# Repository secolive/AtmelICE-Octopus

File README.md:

"Octopus" adapter for Atmel-ICE
===============================

Introduction
------------

this project provides KiCad files for the implementation of an adapter board for use with the Atmel-ICE JTAG debugger.
It provides the following features:

- 0.1" headers with standard pinouts
- Specific VCCIO connector for using a probe
- Jumpers to select VCCIO from the appropriate connectors depending on the use case
- VCCIO comparator and limiter for current nominal voltages: 1.8V, 2.5V, 3.0V, 3.3V, 3.7V, 5.0V
- Voltage boosting to power the LEDs when VCCIO voltages below 3.3V are used

### Motivation

The Atmel-ICE provides two 0.05" headers, for which it's unfortunately difficult to get the appropriate cables. Some
versions of the Atmel-ICE come with a "squid" adapter, but are significantly more expensive.

Boards
------

This project contains two different boards that will assemble and work together as a single "product":

- ATMEL-ICE-Octopus: this is the main adapter board, including all circuits implementing VCCIO selection and limiting

- JTAG-MINI_ADAPTER: 0.1" to 0.05" adapter for standard 10-pin JTAG connectors

Connectors
----------

The following connectors are provided by the Octopus:
- J11: 20-pin 0.1" Multi-ICE JTAG header
- J12: 10-pin 0.1" JTAG connector for ARM
- J13: 10-pin 0.1" JTAG connector for Atmel AVR
- J14: 6-pin 0.1" connector for misc AVR protocols: SPI, debugWire, aWire, PDI, UPDI, TPI
- J15: 4-pin 0.1" header matching Arduino's SWD port
- J16: 1-pin 0.1" header to use as VCCIO probe, typically in conjunction with J15 which does not provide any VCCIO;
  note that J15&J16 together work as a 6-pin 0.1" header combining SWD with VCCIO probe
- J17: 2-pin 0.1" socket to be used for adhoc connections
- J18: 6-pin 0.1" socket to be used for adhoc connections
- J6: 1-pin 0.1" socket to be used as a test point for the VTG provided to Atmel-ICE

VCCIO
-----

The Atmel-ICE needs to be fed with the VCCIO corresponding to the board under test, so that it will work at the same
logic level as the CPU being inspected.

To avoid damage to your CPU, it is important that the VCCIO that the Atmel-ICE uses does not exceed the level actually
used by the board. The octopus helps providing safety as follows:

- The reference VCCIO voltage can come from one of three sources, depending on your use case; these sources are: the
  JTAG connectors, the AVR misc connector, and the VCCIO probe. Use the appropriate source depending in your use case
  to ensure that you're using the VCCIO that matches the component you're connecting to.

- Select the appropriate source using the corresponding jumper; common use cases are:
    * when using a JTAG cable: put the jumper in the JTAG position;
    * when using the AVR misc cable, and your board runs on 5.0V: put the jumper in the SPI position;
    * when using the AVR misc cable, and your board runs on something else than 5.0V: put the jumper in the PROBE
      position, and use the PROBE connector in addition to the SPI cable;
    * when using the SWD cable: put the jumper in the PROBE position, and use the PROBE connector in addition to the SPI
      cable.

- You need to further configure the nominal voltage you're expecting to use with your device, using the appropriate
  jumper. The on-board detection logic will use this configuration to decide whether it is safe to propagate the VCCIO
  voltage to the Atmel-ICE VTG input, as follows:
    * if the input VCCIO matches the nominal voltage range, it is send to the Atmel-ICE, and the green "OK" LED will
      be lit;
    * if the input VCCIO is below the nominal voltage range, it is send to the Atmel-ICE nevertheless, but the amber
      "Below" LED will be lit;
    * otherwise, i.e. if the input VCCIO is above the nominal voltage range, no voltage is sent to the Atmel-ICE, because
      it is considered as a fault which could result in using a voltage higher than the expected VCCIO of the target
      device. In this case, the red "Above" LED will be lit.

Simplified Variants
-------------------

Depending on your use cases, you might not need all the features of the board; for example, perhaps you  need only the
various 0.1" connectors, but don't care about the voltage limiting. Reducing the feature set enables you to skip some
components and hence reduce the cost. Three features are optional:

- VCCIO monitoring and limiting; this main feature can by bypassed altogether, and the selected VCCIO can be sent
  directly as VTG to the Atmel-ICE. You will then have to ensure that you select the proper VCCIO signal, and that it
  does not exceed the target device voltage.

- Status output of the VCCIO monitoring and limiting; obviously, if you don't perform any monitoring and limiting, you
  won't need any status LEDs. Note that it's technically possible to have some voltage monitoring, without limiting,
  meaning VCCIO will always be sent as VTG to the Atmel-ICE, but the Above/OK/Below LEDs will still indicate whether the
  voltage is in the intended range.

- Voltage boosting to power LEDs when input voltage is below 3.3V. Obviously, if you don't want any status LEDs, you
  don't need any voltage boosting.

Altogether, this means the following variants are possible:

- Variant 1a: VCCIO limiting, monitoring with LEDS, voltage boosting
- Variant 1b: VCCIO limiting, monitoring with LEDS, no voltage boosting
- Variant 2a: VCCIO monitoring with LEDs, no limiting, voltage boosting
- Variant 2b: VCCIO monitoring with LEDs, no limiting, no voltage boosting
- Variant 3: VCCIO limiting, no monitoring, no LEDs
- Variant 4: no VCCIO limiting, no monitoring, no LEDs

The following table describes, for which variant, which components can be skipped, and how to position the solder
jumpers JP1 and JP2.

| Variant | *10-*39       | *40-*49            | *50-*59 | *60-*79 | *80-*89 | JP1 2-3 | JP2 2-3 |
|---------|---------------|--------------------|---------|---------|---------|---------|---------|
| 1a      |               |                    |         |         |         |         |         |
| 1b      |               |                    |         |  skip   |         |         |    X    |
| 2a      | skip Q12, C12 |                    |  skip   |         |         |    X    |         |
| 2b      | skip Q12, C12 |                    |  skip   |  skip   |         |    X    |    X    |
| 3       |               | skip Q41, R41, *42 |         |  skip   |  skip   |         |         |
| 4       | skip          | skip               |  skip   |  skip   |  skip   |    X    |         |

Note that wildcards are used to designate any component with the given number, and when ranges are provided, any
component of any type within the given number range should be skipped. The JP columns indicate when the corresponding
jumper needs to have its pads 2 and 3 bridged.

Regarding JP1 and JP2, note that by default they are always bridged in the 1-2 position. It is not necessary to cut this
traced bridging, as long as the corresponding components are skipped according to the table above.

!! Do not forget to verify the proper jumper settings when adding new components to the board, e.g. in a later stage !!

Assembling
----------

The main board is composed of two different parts; when looking at the front:
- the right-hand side contains the black plate, which is meant to be connected to the Atmel-ICE
- the main part is the squid adapter itself

The back plate can be separated from the main part by breaking off the two break tabs. Connect the back plate to the 
main plate using angled 2mm-pitch headers. 

The assembled octopus adapter can then be plugged atop the Atmel-ICE; both products can be assembled using 8mm-long
spacers using M2.5 threads and screws (plastic recommended), as follows:

On the target device, use the adapter when using a standard Atmel 0.05" header; the adapter is designed to fit an
Arduino Due board and not collide with a shield, as follows:

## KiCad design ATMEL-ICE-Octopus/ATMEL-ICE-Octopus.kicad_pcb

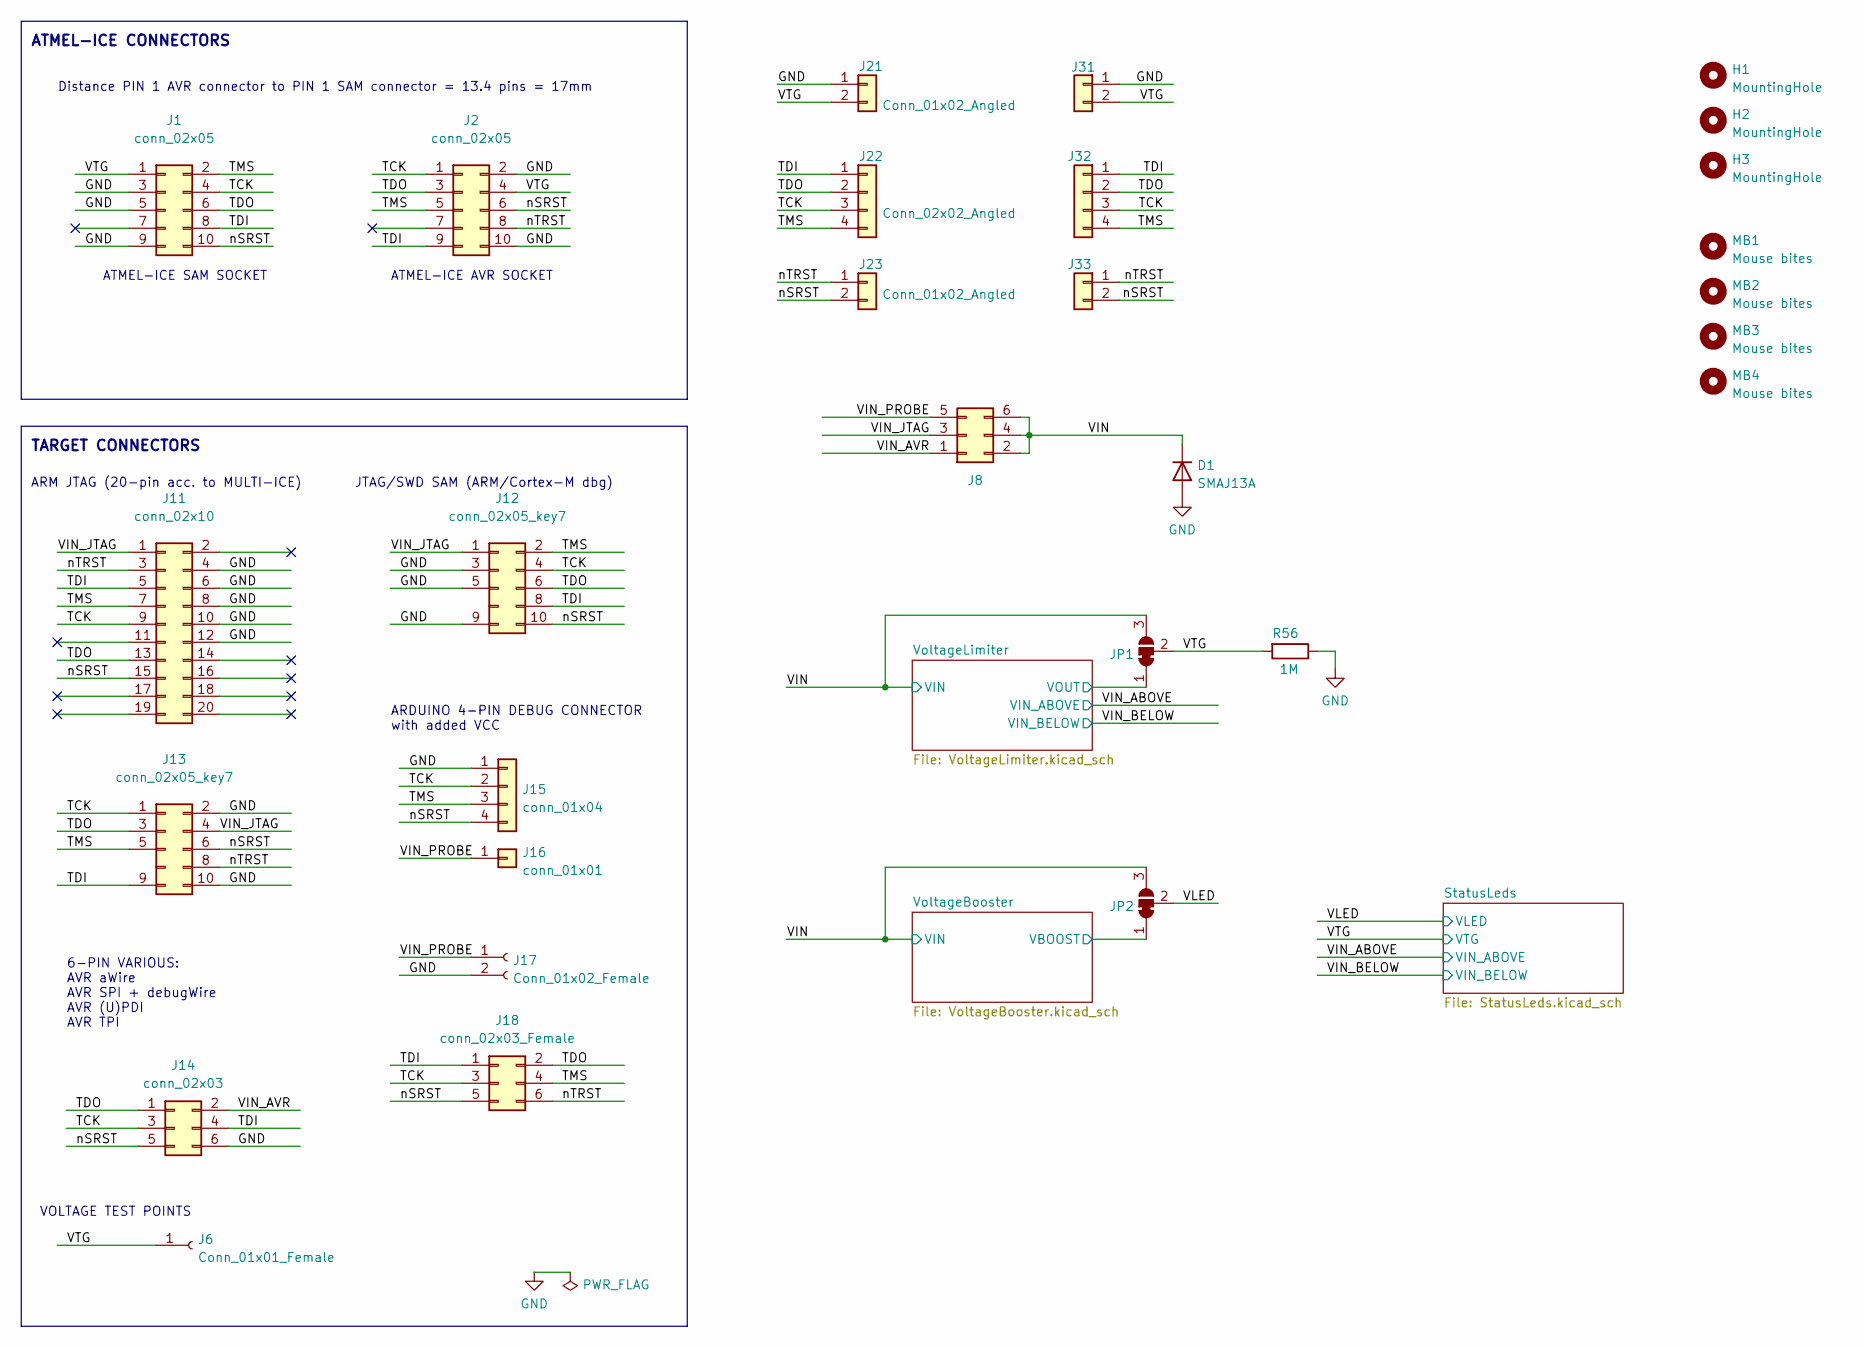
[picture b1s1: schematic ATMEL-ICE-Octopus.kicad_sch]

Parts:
D1: SMAJ13A; D_SMA+SMP_Handsoldering
H1, H2, H3: MountingHole; MountingHole_2.5mm
J1, J2: conn_02x05; PinSocket_2x05_P1.27mm_Vertical_AtmelICE_WithTab
J6: Conn_01x01_Female; PinSocket_1x01_P2.54mm_Vertical
J8: PinHeader_2x03_P2.54mm_Horizontal_Jumper
J11: conn_02x10; IDC-Header_2x10_P2.54mm_Vertical
J12, J13: conn_02x05_key7; IDC-Header_2x05_P2.54mm_Vertical_Key7
J14: conn_02x03; IDC-Header_2x03_P2.54mm_Vertical
J15: conn_01x04; PinHeader_1x04_P2.54mm_Vertical
J16: conn_01x01; PinHeader_1x01_P2.54mm_Vertical
J17: Conn_01x02_Female; PinSocket_1x02_P2.54mm_Vertical
J18: conn_02x03_Female; PinSocket_2x03_P2.54mm_Vertical
J21, J23: Conn_01x02_Angled; PinHeader_1x02_P2.00mm_Horizontal
J22: Conn_02x02_Angled; PinHeader_2x02_P2.00mm_Horizontal
J31, J33: Conn_01x02_Angled; PinHeader_1x02_P2.00mm_Angled
J32: Conn_02x02_Angled; PinHeader_2x02_P2.00mm_Angled
JP1, JP2: SolderJumper_3_Bridged12; SolderJumper-3_P1.3mm_Bridged2Bar12_RoundedPad1.0x1.5mm_Num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
MB1, MB2, MB3, MB4: Mouse bites; mouse-bite-3x4mm-slot
R56: 1M; R_0805_2012Metric_Pad1.20x1.40mm_HandSolder

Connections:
/TCK: J1.4, J2.1, J11.9, J12.4, J13.1, J14.3, J15.2, J18.3, J22.3, J32.3
/TDI: J1.8, J2.9, J11.5, J12.8, J13.9, J14.4, J18.1, J22.1, J32.1
/TDO: J1.6, J2.3, J11.13, J12.6, J13.3, J14.1, J18.2, J22.2, J32.2
/TMS: J1.2, J2.5, J11.7, J12.2, J13.5, J15.3, J18.4, J22.4, J32.4
/VIN: D1.1 (K), J8.2, J8.4, J8.6, JP1.3 (B), JP2.3 (B); also elsewhere on the board
/VIN_AVR: J8.1, J14.2
/VIN_JTAG: J8.3, J11.1, J12.1, J13.4
/VIN_PROBE: J8.5, J16.1, J17.1
/VLED: JP2.2 (C); also elsewhere on the board
/VTG: J1.1, J2.4, J6.1, J21.2, J31.2, JP1.2 (C), R56.2; also elsewhere on the board
/VoltageBooster/VBOOST: JP2.1 (A); also elsewhere on the board
/VoltageLimiter/VOUT: JP1.1 (A); also elsewhere on the board
/nSRST: J1.10, J2.6, J11.15, J12.10, J13.6, J14.5, J15.4, J18.5, J23.2, J33.2
/nTRST: J2.8, J11.3, J13.8, J18.6, J23.1, J33.1
GND: D1.2 (A), J1.3, J1.5, J1.9, J2.2, J2.10, J11.4, J11.6, J11.8, J11.10, J11.12, J12.3, J12.5, J12.9, J13.2, J13.10, J14.6, J15.1, J17.2, J21.1, J31.1, R56.1; also elsewhere on the board

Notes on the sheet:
ARDUINO 4-PIN DEBUG CONNECTOR with added VCC
Distance PIN 1 AVR connector to PIN 1 SAM connector = 13.4 pins = 17mm
6-PIN VARIOUS: AVR aWire AVR SPI + debugWire AVR (U)PDI AVR TPI
ARM JTAG (20-pin acc. to MULTI-ICE)
ATMEL-ICE CONNECTORS
ATMEL-ICE AVR SOCKET
VOLTAGE TEST POINTS
TARGET CONNECTORS
ATMEL-ICE SAM SOCKET
JTAG/SWD SAM (ARM/Cortex-M dbg)

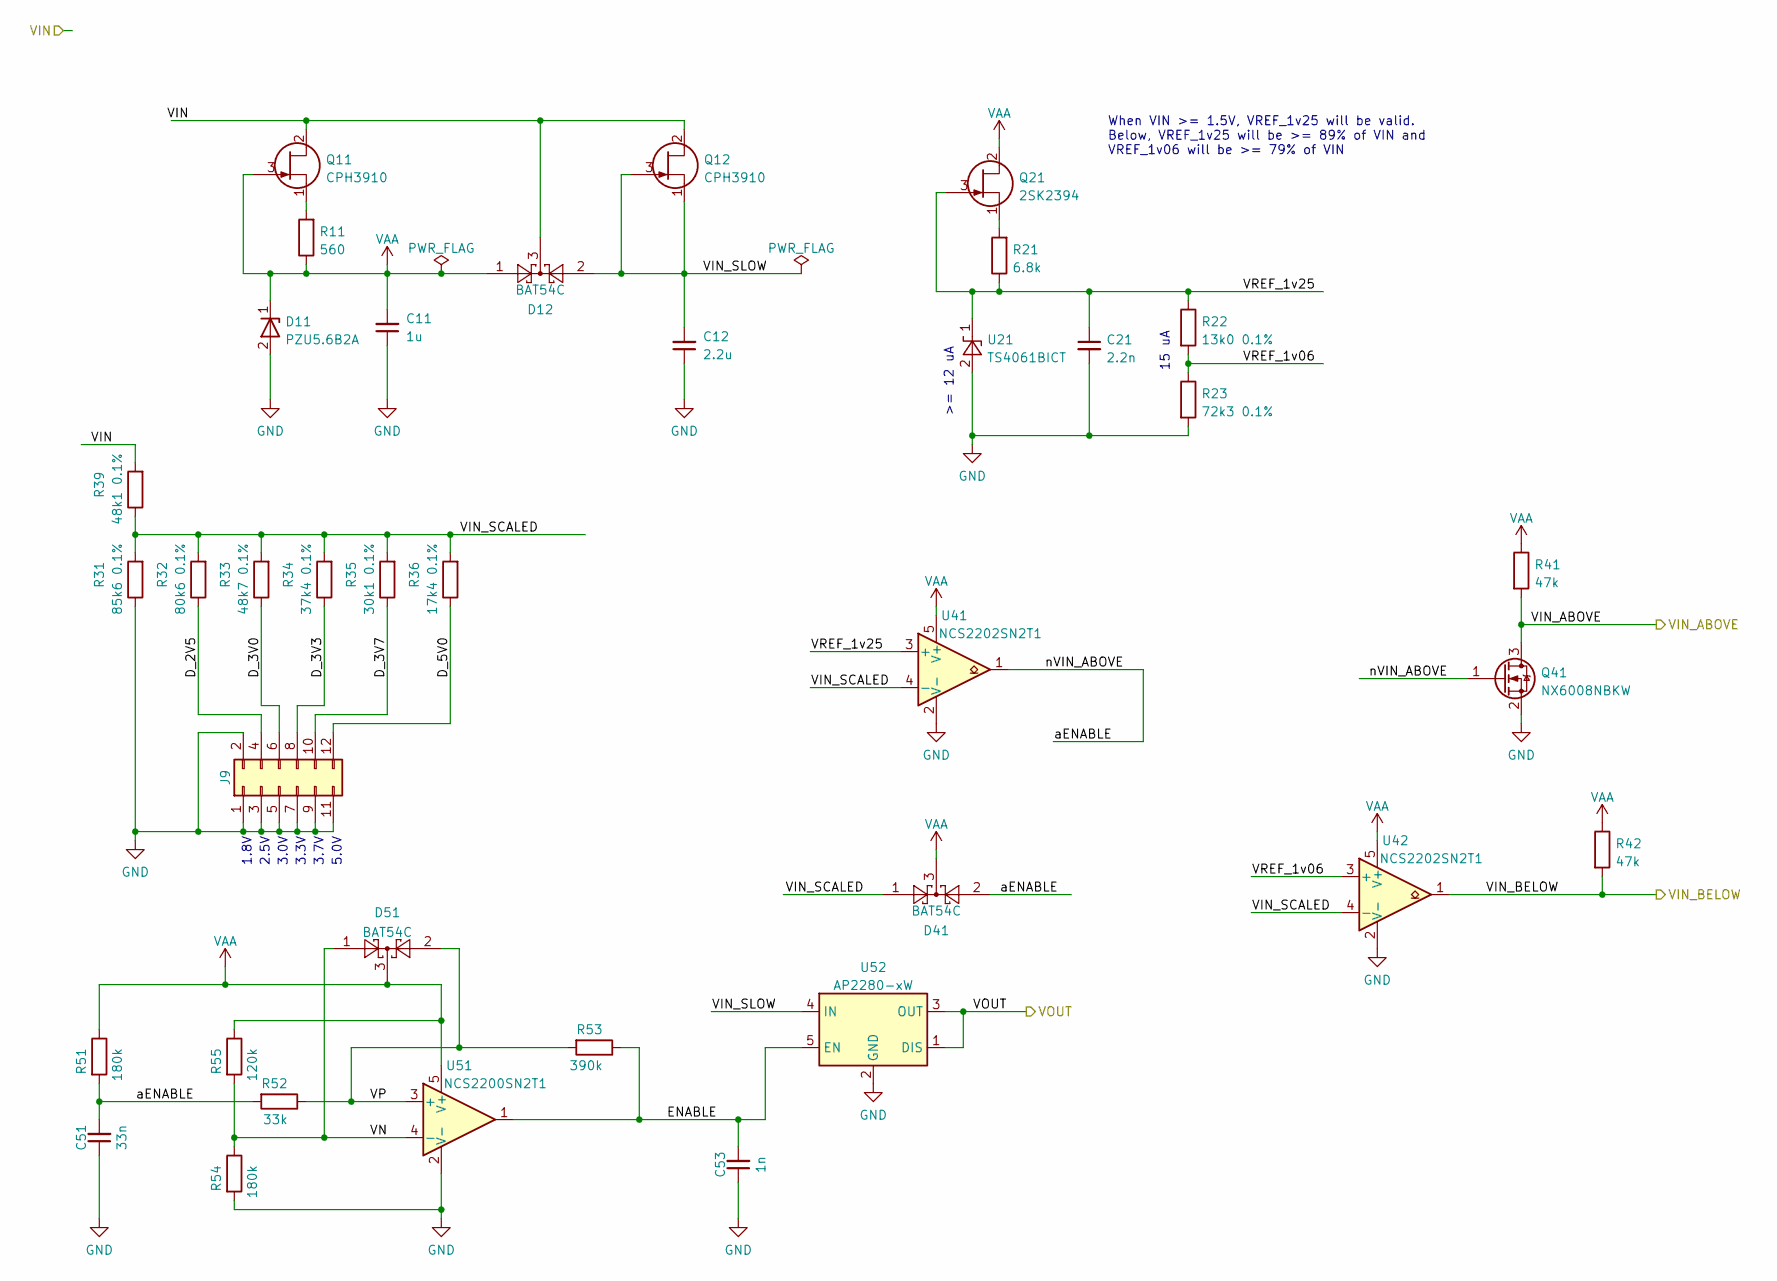
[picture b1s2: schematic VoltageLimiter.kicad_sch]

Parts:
C11: 1u; C_0805_2012Metric_Pad1.18x1.45mm_HandSolder
C12: 2.2u; C_0805_2012Metric_Pad1.18x1.45mm_HandSolder
C21: 2.2n; C_0805_2012Metric_Pad1.18x1.45mm_HandSolder
C51: 33n; C_0805_2012Metric_Pad1.18x1.45mm_HandSolder
C53: 1n; C_0805_2012Metric_Pad1.18x1.45mm_HandSolder
D11: PZU5.6B2A; D_SOD-323_HandSoldering
D12, D41, D51: BAT54C; SOT-23_Handsoldering
J9: PinHeader_2x06_P2.54mm_Horizontal_Jumper
Q11, Q12: CPH3910; SOT-23_Handsoldering
Q21: 2SK2394; SOT-23_Handsoldering
Q41: NX6008NBKW; SOT-323_SC-70_Handsoldering
R11: 560; R_0805_2012Metric_Pad1.20x1.40mm_HandSolder
R21: 6.8k; R_0805_2012Metric_Pad1.20x1.40mm_HandSolder
R22: 13k0 0.1%; R_0805_2012Metric_Pad1.20x1.40mm_HandSolder
R23: 72k3 0.1%; R_0805_2012Metric_Pad1.20x1.40mm_HandSolder
R31: 85k6 0.1%; R_0805_2012Metric_Pad1.20x1.40mm_HandSolder
R32: 80k6 0.1%; R_0805_2012Metric_Pad1.20x1.40mm_HandSolder
R33: 48k7 0.1%; R_0805_2012Metric_Pad1.20x1.40mm_HandSolder
R34: 37k4 0.1%; R_0805_2012Metric_Pad1.20x1.40mm_HandSolder
R35: 30k1 0.1%; R_0805_2012Metric_Pad1.20x1.40mm_HandSolder
R36: 17k4 0.1%; R_0805_2012Metric_Pad1.20x1.40mm_HandSolder
R39: 48k1 0.1%; R_0805_2012Metric_Pad1.20x1.40mm_HandSolder
R41, R42: 47k; R_0805_2012Metric_Pad1.20x1.40mm_HandSolder
R51, R54: 180k; R_0805_2012Metric_Pad1.20x1.40mm_HandSolder
R52: 33k; R_0805_2012Metric_Pad1.20x1.40mm_HandSolder
R53: 390k; R_0805_2012Metric_Pad1.20x1.40mm_HandSolder
R55: 120k; R_0805_2012Metric_Pad1.20x1.40mm_HandSolder
U21: TS4061BICT; SOT-323_SC-70_Handsoldering
U41, U42: NCS2202SN2T1; SOT-23-5_HandSoldering
U51: NCS2200SN2T1; SOT-23-5_HandSoldering
U52: AP2280-xW; SOT-23-5_HandSoldering

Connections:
/VIN: D12.3, Q11.2 (D), Q12.2 (D), R39.2; also elsewhere on the board
/VIN_ABOVE: Q41.3 (D), R41.2; also elsewhere on the board
/VIN_BELOW: R42.2, U42.1; also elsewhere on the board
/VoltageLimiter/D_2V5: J9.4, R32.1
/VoltageLimiter/D_3V0: J9.6, R33.1
/VoltageLimiter/D_3V3: J9.8, R34.1
/VoltageLimiter/D_3V7: J9.10, R35.1
/VoltageLimiter/D_5V0: J9.12, R36.1
/VoltageLimiter/ENABLE: C53.2, R53.1, U51.1, U52.5 (EN)
/VoltageLimiter/VIN_SCALED: D41.1, R31.2, R32.2, R33.2, R34.2, R35.2, R36.2, R39.1, U41.4 (-), U42.4 (-)
/VoltageLimiter/VIN_SLOW: C12.2, D12.2, Q12.1 (S), Q12.3 (G), U52.4 (IN)
/VoltageLimiter/VN: D51.1, R54.1, R55.2, U51.4 (-)
/VoltageLimiter/VOUT: U52.1 (DIS), U52.3 (OUT); also elsewhere on the board
/VoltageLimiter/VP: D51.2, R52.1, R53.2, U51.3 (+)
/VoltageLimiter/VREF_1v06: R22.2, R23.1, U42.3 (+)
/VoltageLimiter/VREF_1v25: C21.1, Q21.3 (G), R21.1, R22.1, U21.1 (K), U41.3 (+)
/VoltageLimiter/aENABLE: C51.2, D41.2, Q41.1 (G), R51.2, R52.2, U41.1
GND: C11.1, C12.1, C21.2, C51.1, C53.1, D11.2 (A), J9.1, J9.2, J9.3, J9.5, J9.7, J9.9, J9.11, Q41.2 (S), R23.2, R31.1, R54.2, U21.2 (A), U41.2 (V-), U42.2 (V-), U51.2 (V-), U52.2 (GND); also elsewhere on the board
unnamed: Q11.1 (S), R11.2
unnamed: Q21.1 (S), R21.2
VAA: C11.2, D11.1 (K), D12.1, D41.3, D51.3, Q11.3 (G), Q21.2 (D), R11.1, R41.1, R42.1, R51.1, R55.1, U41.5 (V+), U42.5 (V+), U51.5 (V+)

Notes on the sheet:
15 uA
3.7V
When VIN >= 1.5V, VREF_1v25 will be valid. Below, VREF_1v25 will be >= 89% of VIN and VREF_1v06 will be >= 79% of VIN
2.5V
3.0V
1.8V
>= 12 uA
5.0V
3.3V

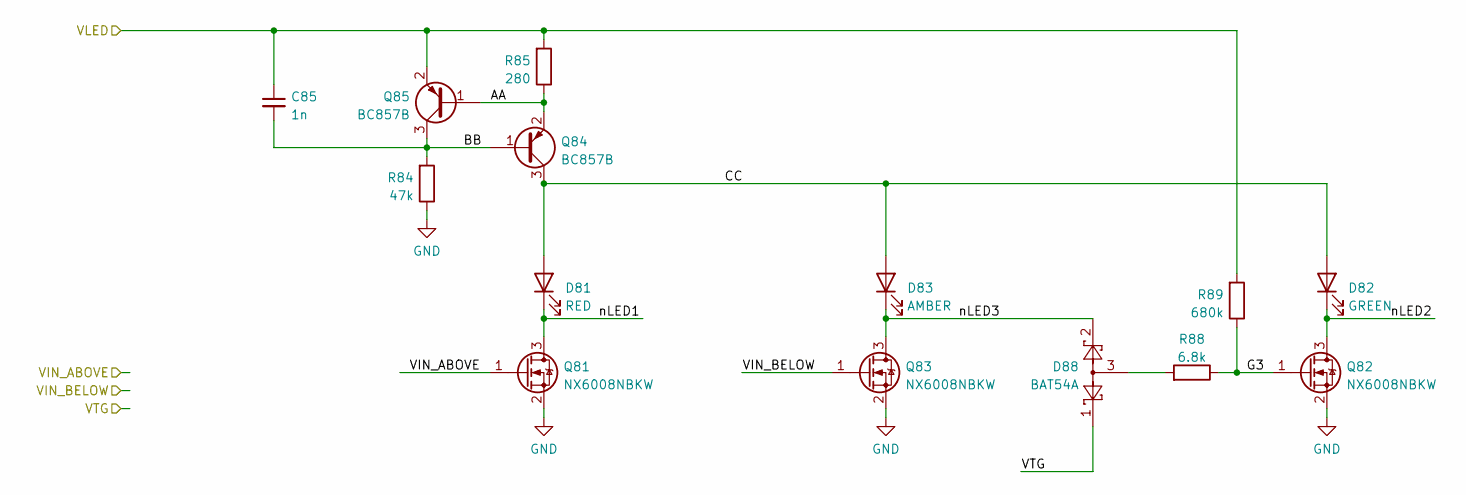
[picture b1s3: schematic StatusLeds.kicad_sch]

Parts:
C85: 1n; C_0805_2012Metric_Pad1.18x1.45mm_HandSolder
D81: RED; LED_0805_2012Metric_Pad1.15x1.40mm_HandSolder
D82: GREEN; LED_0805_2012Metric_Pad1.15x1.40mm_HandSolder
D83: AMBER; LED_0805_2012Metric_Pad1.15x1.40mm_HandSolder
D88: BAT54A; SOT-23_Handsoldering
Q81, Q82, Q83: NX6008NBKW; SOT-323_SC-70_Handsoldering
Q84, Q85: BC857B; SOT-23_Handsoldering
R84: 47k; R_0805_2012Metric_Pad1.20x1.40mm_HandSolder
R85: 280; R_0805_2012Metric_Pad1.20x1.40mm_HandSolder
R88: 6.8k; R_0805_2012Metric_Pad1.20x1.40mm_HandSolder
R89: 680k; R_0805_2012Metric_Pad1.20x1.40mm_HandSolder

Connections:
/StatusLeds/AA: Q84.2 (E), Q85.1 (B), R85.1
/StatusLeds/BB: C85.2, Q84.1 (B), Q85.3 (C), R84.2
/StatusLeds/CC: D81.2 (A), D82.2 (A), D83.2 (A), Q84.3 (C)
/StatusLeds/G3: Q82.1 (G), R88.1, R89.1
/StatusLeds/nLED1: D81.1 (K), Q81.3 (D)
/StatusLeds/nLED2: D82.1 (K), Q82.3 (D)
/StatusLeds/nLED3: D83.1 (K), D88.2, Q83.3 (D)
/VIN_ABOVE: Q81.1 (G); also elsewhere on the board
/VIN_BELOW: Q83.1 (G); also elsewhere on the board
/VLED: C85.1, Q85.2 (E), R85.2, R89.2; also elsewhere on the board
/VTG: D88.1; also elsewhere on the board
GND: Q81.2 (S), Q82.2 (S), Q83.2 (S), R84.1; also elsewhere on the board
unnamed: D88.3, R88.2

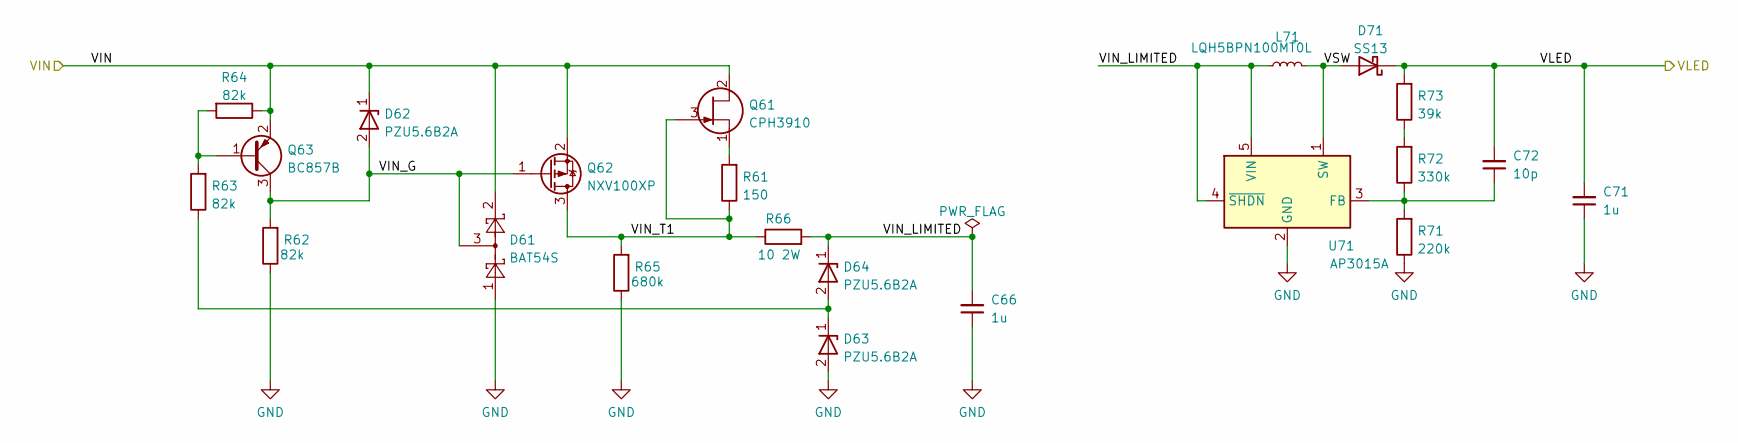
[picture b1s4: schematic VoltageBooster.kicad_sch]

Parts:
C66, C71: 1u; C_0805_2012Metric_Pad1.18x1.45mm_HandSolder
C72: 10p; C_0805_2012Metric_Pad1.18x1.45mm_HandSolder
D61: BAT54S; SOT-23_Handsoldering
D62, D63, D64: PZU5.6B2A; D_SOD-323_HandSoldering
D71: SS13; D_SMA+SMP_Handsoldering
L71: LQH5BPN100MT0L; L_6.5x6.5_H4.5
Q61: CPH3910; SOT-23_Handsoldering
Q62: NXV100XP; SOT-23_Handsoldering
Q63: BC857B; SOT-23_Handsoldering
R61: 150; R_0805_2012Metric_Pad1.20x1.40mm_HandSolder
R62, R63, R64: 82k; R_0805_2012Metric_Pad1.20x1.40mm_HandSolder
R65: 680k; R_0805_2012Metric_Pad1.20x1.40mm_HandSolder
R66: 10 2W; R_2512_6332Metric_Pad1.40x3.35mm_HandSolder
R71: 220k; R_0805_2012Metric_Pad1.20x1.40mm_HandSolder
R72: 330k; R_0805_2012Metric_Pad1.20x1.40mm_HandSolder
R73: 39k; R_0805_2012Metric_Pad1.20x1.40mm_HandSolder
U71: AP3015A; SOT-23-5_HandSoldering

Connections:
/VIN: D61.2, D62.1 (K), Q61.2 (D), Q62.2 (S), Q63.2 (E), R64.1; also elsewhere on the board
/VoltageBooster/VBOOST: C71.2, C72.2, D71.1 (K), R73.2; also elsewhere on the board
/VoltageBooster/VIN_G: D61.3, D62.2 (A), Q62.1 (G), Q63.3 (C), R62.2
/VoltageBooster/VIN_LIMITED: C66.2, D64.1 (K), L71.1, R66.2, U71.4 (~SHDN), U71.5 (VIN)
/VoltageBooster/VIN_T1: Q61.3 (G), Q62.3 (D), R61.1, R65.2, R66.1
/VoltageBooster/VSW: D71.2 (A), L71.2, U71.1 (SW)
GND: C66.1, C71.1, D61.1, D63.2 (A), R62.1, R65.1, R71.1, U71.2 (GND); also elsewhere on the board
unnamed: C72.1, R71.2, R72.1, U71.3 (FB)
unnamed: D63.1 (K), D64.2 (A), R63.1
unnamed: Q61.1 (S), R61.2
unnamed: Q63.1 (B), R63.2, R64.2
unnamed: R72.2, R73.1

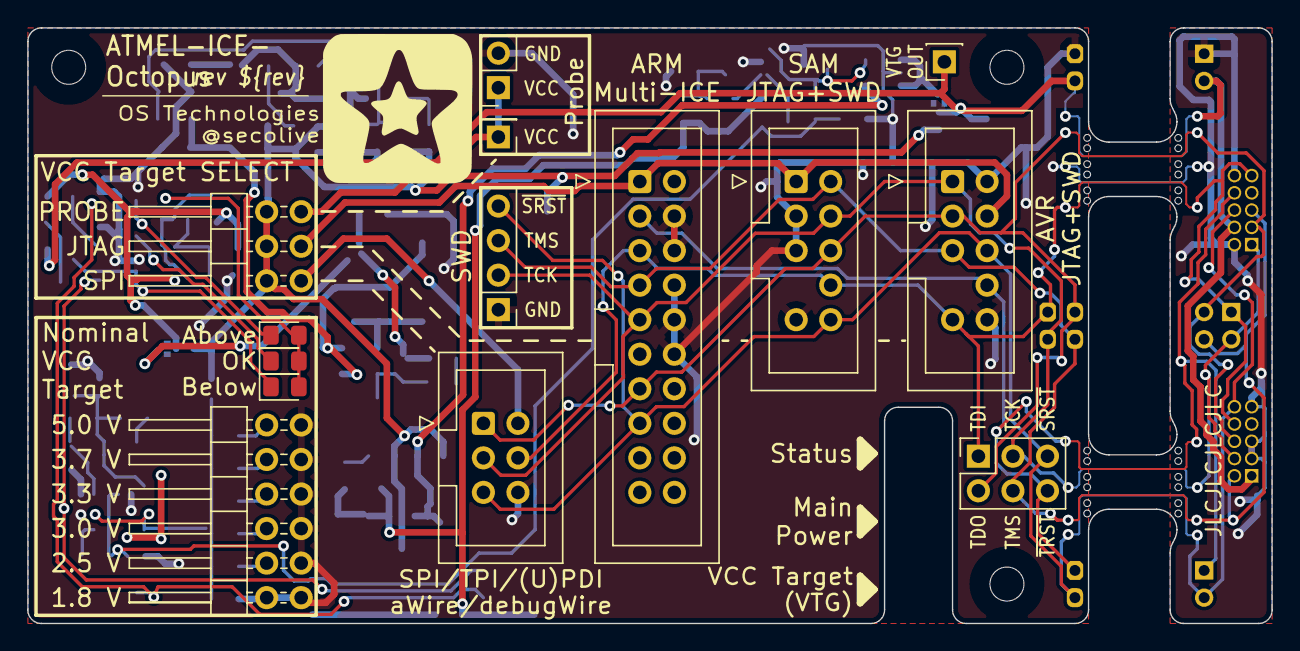
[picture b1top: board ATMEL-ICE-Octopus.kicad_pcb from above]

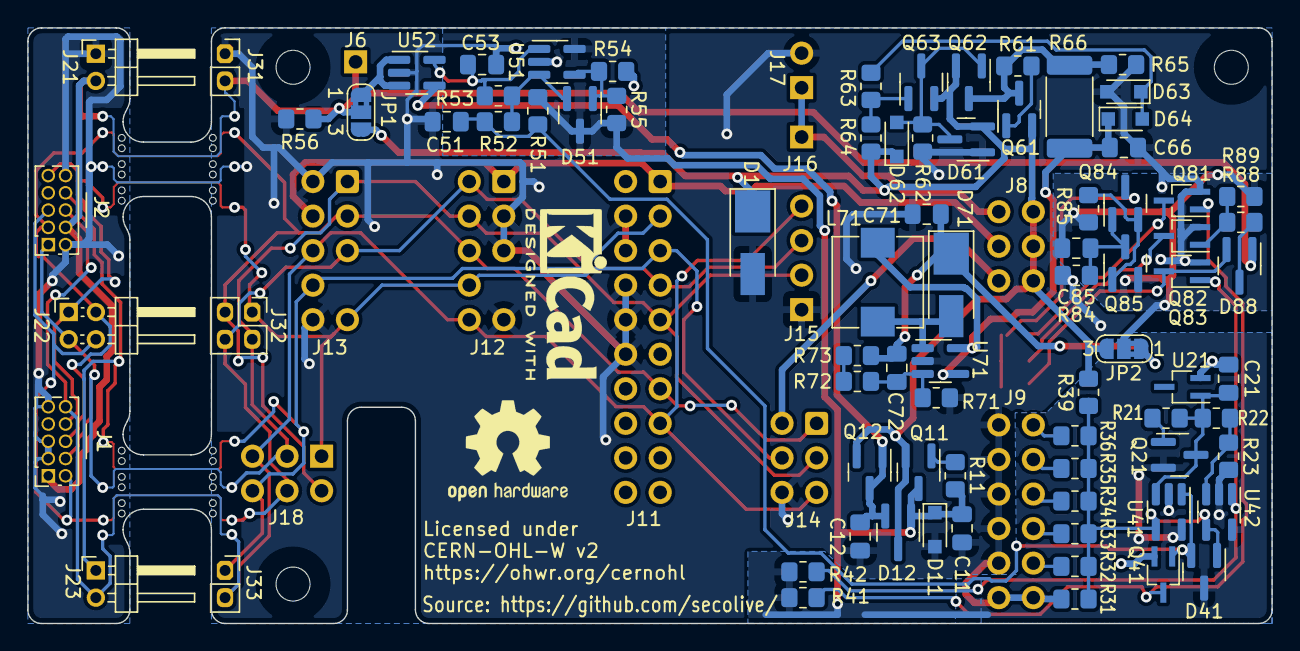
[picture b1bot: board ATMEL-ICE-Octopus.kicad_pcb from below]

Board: 2 copper layers, 91.5 x 43.8 mm, 105 parts (83 on the bottom side), 50 nets.

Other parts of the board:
G1: LOGO
G1#2: OpenHardware Logo; OSHW-Logo2_9.8x8mm_SilkScreen
G3: KiCad logo; KiCad-Logo2_5mm_SilkScreen

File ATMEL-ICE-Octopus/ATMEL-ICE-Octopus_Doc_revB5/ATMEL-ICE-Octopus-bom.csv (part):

"Row";"Part";"Footprint";"Value";"References";"Quantity Per PCB";"Description";"Status"
"1";"C_Small";"C_0805_2012Metric_Pad1.18x1.45mm_HandSolder";"10 pF";"C72";"1";"Unpolarized capacitor, small symbol";" "
"2";"C_Small";"C_0805_2012Metric_Pad1.18x1.45mm_HandSolder";"1 nF";"C53 C85";"2";"Unpolarized capacitor, small symbol";" "
"3";"C_Small";"C_0805_2012Metric_Pad1.18x1.45mm_HandSolder";"2.2 nF";"C21";"1";"Unpolarized capacitor, small symbol";" "
"4";"C_Small";"C_0805_2012Metric_Pad1.18x1.45mm_HandSolder";"33 nF";"C51";"1";"Unpolarized capacitor, small symbol";" "
"5";"C_Small";"C_0805_2012Metric_Pad1.18x1.45mm_HandSolder";"1 µF";"C11 C66 C71";"3";"Unpolarized capacitor, small symbol";" "
"6";"C_Small";"C_0805_2012Metric_Pad1.18x1.45mm_HandSolder";"2.2 µF";"C12";"1";"Unpolarized capacitor, small symbol";" "
"7";"LED";"LED_0805_2012Metric_Pad1.15x1.40mm_HandSolder";"AMBER";"D83";"1";"Light emitting diode";" "
"8";"BAT54A";"SOT-23_Handsoldering";"BAT54A";"D88";"1";"schottky barrier diode";" "
"9";"BAT54C";"SOT-23_Handsoldering";"BAT54C";"D12 D41 D51";"3";"dual schottky barrier diode, common cathode";" "
"10";"BAT54S";"SOT-23_Handsoldering";"BAT54S";"D61";"1";"schottky barrier diode";" "
"11";"LED";"LED_0805_2012Metric_Pad1.15x1.40mm_HandSolder";"GREEN";"D82";"1";"Light emitting diode";" "
"12";"Zener_SOD323";"D_SOD-323_HandSoldering";"PZU5.6B2A";"D11 D62 D63 D64";"4";"Zener diode";" "
"13";"LED";"LED_0805_2012Metric_Pad1.15x1.40mm_HandSolder";"RED";"D81";"1";"Light emitting diode";" "
"14";"D";"D_SMA+SMP_Handsoldering";"SMAJ13A";"D1";"1";"Diode";" "
"15";"D_Schottky";"D_SMA+SMP_Handsoldering";"SS13";"D71";"1";"Schottky diode";" "
"16";"Conn_01x01_Female";"PinSocket_1x01_P2.54mm_Vertical";"Conn_01x01_Female";"J6";"1";"Generic connector, single row, 01x01, script generated (kicad-library-utils/schlib/autogen/connector/)";" "
"17";"Conn_01x02";"PinHeader_1x02_P2.00mm_Horizontal";"Conn_01x02_Angled";"J21 J23";"2";"Generic connector, single row, 01x02, script generated (kicad-library-utils/schlib/autogen/connector/)";" "
"18";"Conn_01x02";"PinHeader_1x02_P2.00mm_Angled";"Conn_01x02_Angled";"J31 J33";"2";"Generic connector, single row, 01x02, script generated (kicad-library-utils/schlib/autogen/connector/)";" "
"19";"Conn_01x02_Female";"PinSocket_1x02_P2.54mm_Vertical";"Conn_01x02_Female";"J17";"1";"Generic connector, single row, 01x02, script generated (kicad-library-utils/schlib/autogen/connector/)";" "
"20";"Conn_01x04";"PinHeader_2x02_P2.00mm_Horizontal";"Conn_02x02_Angled";"J22";"1";"Generic connector, single row, 01x04, script generated (kicad-library-utils/schlib/autogen/connector/)";" "
"21";"Conn_01x04";"PinHeader_2x02_P2.00mm_Angled";"Conn_02x02_Angled";"J32";"1";"Generic connector, single row, 01x04, script generated (kicad-library-utils/schlib/autogen/connector/)";" "
"22";"Conn_01x01";"PinHeader_1x01_P2.54mm_Vertical";"conn_01x01";"J16";"1";"Generic connector, single row, 01x01, script generated (kicad-library-utils/schlib/autogen/connector/)";" "
"23";"Conn_01x04";"PinHeader_1x04_P2.54mm_Vertical";"conn_01x04";"J15";"1";"Generic connector, single row, 01x04, script generated (kicad-library-utils/schlib/autogen/connector/)";" "
"24";"Conn_02x03_Odd_Even";"IDC-Header_2x03_P2.54mm_Vertical";"conn_02x03";"J14";"1";"Generic connector, double row, 02x03, odd/even pin numbering scheme (row 1 odd numbers, row 2 even numbers), script generated (kicad-library-utils/schlib/autogen/connector/)";" "
"25";"Conn_02x03_Odd_Even";"PinSocket_2x03_P2.54mm_Vertical";"conn_02x03_Female";"J18";"1";"Generic connector, double row, 02x03, odd/even pin numbering scheme (row 1 odd numbers, row 2 even numbers), script generated (kicad-library-utils/schlib/autogen/connector/)";" "
"26";"Conn_02x05_Odd_Even";"PinSocket_2x05_P1.27mm_Vertical_AtmelICE_WithTab";"conn_02x05";"J1 J2";"2";"Generic connector, double row, 02x05, odd/even pin numbering scheme (row 1 odd numbers, row 2 even numbers), script generated (kicad-library-utils/schlib/autogen/connector/)";" "
"27";"Conn_JTAG_02x05";"IDC-Header_2x05_P2.54mm_Vertical_Key7";"conn_02x05_key7";"J12 J13";"2";"Generic connector, double row, 02x05, odd/even pin numbering scheme (row 1 odd numbers, row 2 even numbers), script generated (kicad-library-utils/schlib/autogen/connector/)";" "
"28";"Conn_02x10_Odd_Even";"IDC-Header_2x10_P2.54mm_Vertical";"conn_02x10";"J11";"1";"Generic connector, double row, 02x10, odd/even pin numbering scheme (row 1 odd numbers, row 2 even numbers), script generated (kicad-library-utils/schlib/autogen/connector/)";" "
"29";"Conn_02x03_Odd_Even";"PinHeader_2x03_P2.54mm_Horizontal_Jumper";"~";"J8";"1";"Generic connector, double row, 02x03, odd/even pin numbering scheme (row 1 odd numbers, row 2 even numbers), script generated (kicad-library-utils/schlib/autogen/connector/)";" "
"30";"Conn_02x06_Odd_Even";"PinHeader_2x06_P2.54mm_Horizontal_Jumper";"~";"J9";"1";"Generic connector, double row, 02x06, odd/even pin numbering scheme (row 1 odd numbers, row 2 even numbers), script generated (kicad-library-utils/schlib/autogen/connector/)";" "
"31";"L_Small";"L_6.5x6.5_H4.5";"LQH5BPN100MT0L";"L71";"1";"Inductor, small symbol";" "
"32";"2SK2394";"SOT-23_Handsoldering";"2SK2394";"Q21";"1";"N-JFET transistor,  15 V, 10 to 20 mA, 38 mS, -0.3 to -1.0 Vgs(off), SOT23-3";" "
"33";"BC857B";"SOT-23_Handsoldering";"BC857B";"Q63 Q84 Q85";"3";"500mA Ic, 60V Vce, PNP Transistor, SOT-23";" "
"34";"CPH3910";"SOT-23_Handsoldering";"CPH3910";"Q11 Q12 Q61";"3";"N-JFET transistor, 25 V, 20 to 40 mA, 40 mS, -0.6 to -1.8 Vgs(off), SOT23-3";" "
"35";"NX6008NBKW";"SOT-323_SC-70_Handsoldering";"NX6008NBKW";"Q41 Q81 Q82 Q83";"4";"60V Vds, 0.9V Vgs(th) max, 250mA Id, N-Channel MOSFET, SOT-323";" "
"36";"NXV100XP";"SOT-23_Handsoldering";"NXV100XP";"Q62";"1";"P-channel MOSFET -30V, -1.5A";" "
"37";"R";"R_2512_6332Metric_Pad1.40x3.35mm_HandSolder";"10 Ω";"R66";"1";"Resistor";" "
"38";"R";"R_0805_2012Metric_Pad1.20x1.40mm_HandSolder";"150 Ω";"R61";"1";"Resistor";" "
"39";"R";"R_0805_2012Metric_Pad1.20x1.40mm_HandSolder";"280 Ω";"R85";"1";"Resistor";" "
"40";"R";"R_0805_2012Metric_Pad1.20x1.40mm_HandSolder";"560 Ω";"R11";"1";"Resistor";" "
"41";"R";"R_0805_2012Metric_Pad1.20x1.40mm_HandSolder";"6.8 kΩ";"R21 R88";"2";"Resistor";" "
"42";"R";"R_0805_2012Metric_Pad1.20x1.40mm_HandSolder";"13 kΩ";"R22";"1";"Resistor";" "
"43";"R";"R_0805_2012Metric_Pad1.20x1.40mm_HandSolder";"17.4 kΩ";"R36";"1";"Resistor";" "
"44";"R";"R_0805_2012Metric_Pad1.20x1.40mm_HandSolder";"30.1 kΩ";"R35";"1";"Resistor";" "
"45";"R";"R_0805_2012Metric_Pad1.20x1.40mm_HandSolder";"33 kΩ";"R52";"1";"Resistor";" "
"46";"R";"R_0805_2012Metric_Pad1.20x1.40mm_HandSolder";"37.4 kΩ";"R34";"1";"Resistor";" "
"47";"R";"R_0805_2012Metric_Pad1.20x1.40mm_HandSolder";"39 kΩ";"R73";"1";"Resistor";" "
"48";"R";"R_0805_2012Metric_Pad1.20x1.40mm_HandSolder";"47 kΩ";"R41 R42 R84";"3";"Resistor";" "
"49";"R";"R_0805_2012Metric_Pad1.20x1.40mm_HandSolder";"48.1 kΩ";"R39";"1";"Resistor";" "
"50";"R";"R_0805_2012Metric_Pad1.20x1.40mm_HandSolder";"48.7 kΩ";"R33";"1";"Resistor";" "
"51";"R";"R_0805_2012Metric_Pad1.20x1.40mm_HandSolder";"72.3 kΩ";"R23";"1";"Resistor";" "
"52";"R";"R_0805_2012Metric_Pad1.20x1.40mm_HandSolder";"80.6 kΩ";"R32";"1";"Resistor";" "
"53";"R";"R_0805_2012Metric_Pad1.20x1.40mm_HandSolder";"82 kΩ";"R62 R63 R64";"3";"Resistor";" "
"54";"R";"R_0805_2012Metric_Pad1.20x1.40mm_HandSolder";"85.6 kΩ";"R31";"1";"Resistor";" "
"55";"R";"R_0805_2012Metric_Pad1.20x1.40mm_HandSolder";"120 kΩ";"R55";"1";"Resistor";" "
"56";"R";"R_0805_2012Metric_Pad1.20x1.40mm_HandSolder";"180 kΩ";"R51 R54";"2";"Resistor";" "
"57";"R";"R_0805_2012Metric_Pad1.20x1.40mm_HandSolder";"220 kΩ";"R71";"1";"Resistor";" "
"58";"R";"R_0805_2012Metric_Pad1.20x1.40mm_HandSolder";"330 kΩ";"R72";"1";"Resistor";" "
"59";"R";"R_0805_2012Metric_Pad1.20x1.40mm_HandSolder";"390 kΩ";"R53";"1";"Resistor";" "
"60";"R";"R_0805_2012Metric_Pad1.20x1.40mm_HandSolder";"680 kΩ";"R65 R89";"2";"Resistor";" "
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
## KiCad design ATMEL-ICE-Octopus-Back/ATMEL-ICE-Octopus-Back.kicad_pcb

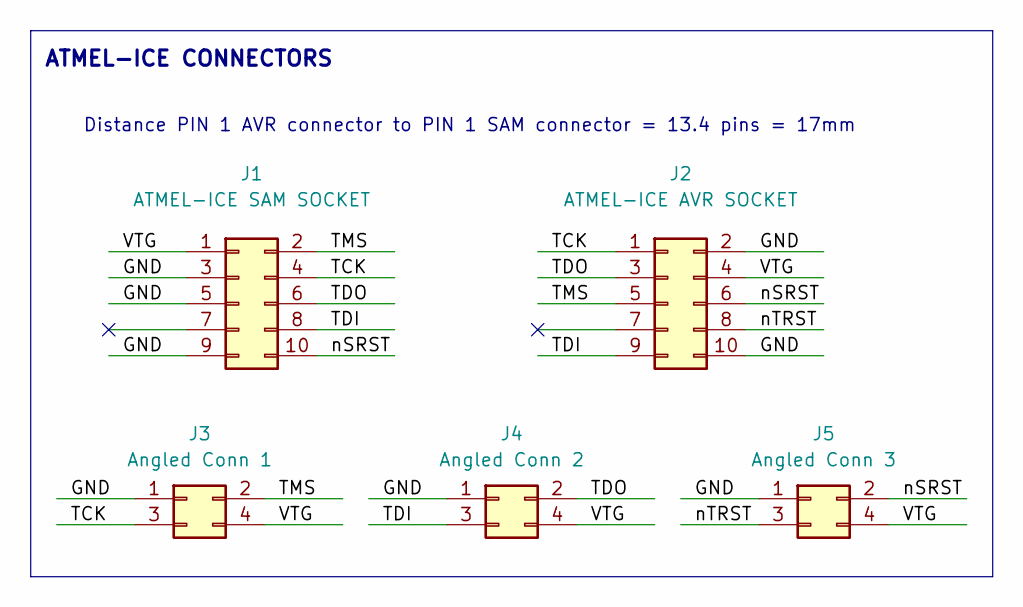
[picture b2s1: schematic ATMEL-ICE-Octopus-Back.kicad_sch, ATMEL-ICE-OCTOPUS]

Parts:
J1: ATMEL-ICE SAM SOCKET; PinSocket_2x05_P1.27mm_Vertical_AtmelICE_WithTab
J2: ATMEL-ICE AVR SOCKET; PinSocket_2x05_P1.27mm_Vertical_AtmelICE_WithTab
J3: Angled Conn 1; PinHeader_2x02_P2.54mm_Vertical_NoSilk
J4: Angled Conn 2; PinHeader_2x02_P2.54mm_Vertical_NoSilk
J5: Angled Conn 3; PinHeader_2x02_P2.54mm_Vertical_NoSilk

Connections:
/GND: J1.3, J1.5, J1.9, J2.2, J2.10, J3.1, J4.1, J5.1
/TCK: J1.4, J2.1, J3.3
/TDI: J1.8, J2.9, J4.3
/TDO: J1.6, J2.3, J4.2
/TMS: J1.2, J2.5, J3.2
/VTG: J1.1, J2.4, J3.4, J4.4, J5.4
/nSRST: J1.10, J2.6, J5.2
/nTRST: J2.8, J5.3

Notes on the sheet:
Distance PIN 1 AVR connector to PIN 1 SAM connector = 13.4 pins = 17mm
ATMEL-ICE CONNECTORS

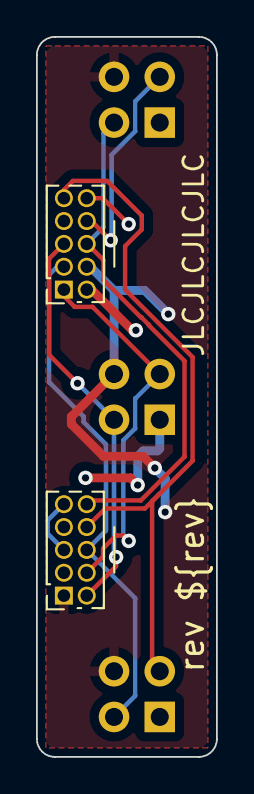
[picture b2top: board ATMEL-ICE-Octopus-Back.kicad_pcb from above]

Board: 2 copper layers, 10.0 x 40.0 mm, 5 parts (0 on the bottom side), 8 nets.

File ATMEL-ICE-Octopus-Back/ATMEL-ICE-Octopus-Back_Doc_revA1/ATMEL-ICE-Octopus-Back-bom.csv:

"Row";"Part";"Footprint";"Value";"References";"Quantity Per PCB";"Description";"Status"
"1";"Conn_02x05_Odd_Even";"PinSocket_2x05_P1.27mm_Vertical_AtmelICE_WithTab";"ATMEL-ICE SAM SOCKET";"J1 J2";"2";"Generic connector, double row, 02x05, odd/even pin numbering scheme (row 1 odd numbers, row 2 even numbers), script generated (kicad-library-utils/schlib/autogen/connector/)";" "
"2";"Conn_02x02_Odd_Even";"PinHeader_2x02_P2.54mm_Vertical_NoSilk";"Angled Conn 1";"J3 J4 J5";"3";"Generic connector, double row, 02x02, odd/even pin numbering scheme (row 1 odd numbers, row 2 even numbers), script generated (kicad-library-utils/schlib/autogen/connector/)";" "





"Project info:"
"Schematic:";"ATMEL-ICE-Octopus-Back"
"Variant:";"default"
"Revision:";"A1"
"Date:";"2022-06-21_16-46-35"
"KiCad Version:";"(6.0.2-0)"
"Statistics:"
"Component Groups:";"2"
"Component Count:";"5"
"Fitted Components:";"5"
"Number of PCBs:";"1"
"Total Components:";"5"

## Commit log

2022-06-14 ATMEL-ICE-Octopus-backups: rev A0
2022-06-14 JTAG-MINI_ADAPTER: rev A0
2022-06-21 ATMEL-ICE-Octopus: rev A1 - add OHL license and use kibot
2022-06-21 ATMEL-ICE-Octopus-Back: rev A1 - add OHL license and use kibot
2022-06-21 JTAG-MINI-ADAPTER: rev A1 - add OHL license and use kibot
2022-06-21 Addition of README.md and LICENSE
2022-12-22 ATMEL-ICE-Octopus: rev B5
2023-01-09 ATMEL-ICE-Octopus: rev B6
2023-01-10 Documentation update to match revB6

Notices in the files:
ATMEL-ICE-Octopus/ATMEL-ICE-Octopus.kicad_pcb:
Licensed under
CERN-OHL-W v2
parts and their libraries:
license: Licensed under CERN-OHL-W v2
